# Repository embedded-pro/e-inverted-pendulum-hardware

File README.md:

# e-inverted-pendulum — Hardware

Hardware for the [e-inverted-pendulum](https://github.com/embedded-pro/e-inverted-pendulum) two-wheeled self-balancing
robot. The PCB is the robot's chassis: one vertical 85 × 130 mm 4-layer board carries the electronics, the battery and
the motor bracket. Built and assembled at JLCPCB.

This repository holds the **KiCad** design, the Python scripts that generate the schematic and sync the board, and the
ngspice simulation suite. The firmware lives in its own repository and is the source of the requirements.

> **Status: Phase 3 (layout), placement handed to the owner (D-032).** Phases 0–2 (requirements, schematic,
> simulation) are signed off. The schematic is complete, simulated and ERC-clean; the board has its outline, rule
> areas and bracket holes, with every part in the staging area. See [docs/plan.md](docs/plan.md) for the phase gates.

---

## Highlights

- **STM32WB55RGV6** with BLE 5: internal SMPS, 32 MHz HSE without external caps, printed IFA through an
  `MLPF-WB55-01E3` filter on a 50 Ω GCPW line, DNP pi tuning and a DNP U.FL test port.
- **DRV8711 gate driver with four external half-bridges** (`CSD88537ND`) for two MG310 gear motors: indexer bypassed
  (PWMMODE 1), 50 mΩ low-side shunts with Kelvin taps, 2.0 A trip, SS34 clamps on every phase node.
- **Battery path:** XT30, 4 A fuse, back-to-back `AO4805` P-FETs for reverse polarity and switching, with a simulated
  Miller soft start; `SMBJ15A` after the FETs.
- **Rails:** `TPS62933F` buck to 5 V (encoders, RGB LEDs, LDO), `TLV75533P` LDO to 3.3 V, ferrite-filtered VDDA.
- **12 RGB LEDs** (`WS2812B-2020-V6`) on one PA7 timer/DMA pin through a 5 V `SN74AHCT1G125`: it is also a toy (D-035).
  No buttons, no buzzer.
- **Test pads** on every sheet (rails, motor phases and shunts, PWM, SPI, encoders, IMU, I2C), net names on the silk.
- **Sensors and storage:** `MPU-6500` IMU on SPI2, `W25Q16JV` flash on SPI1, `M24C64` EEPROM and an `ST25DV04KC` NFC tag
  with a printed 13.56 MHz coil on I2C3, plus a Qwiic port.
- **Encoder inputs:** ESD at the connector, 100 Ω + 1 nF, `SN74LVC3G17` Schmitt buffers with 5 V-tolerant inputs.

---

## Board architecture

The schematic has 8 hierarchical sheets, one functional block each, drawn as titled boxes with design notes (the
e-psu-hardware pattern, D-033):

| Sheet | Function | Key parts |
|-------|----------|-----------|
| `e-inverted-pendulum.kicad_sch` | Root: sheet descriptions, power flow, grounding | — |
| `power_entry` | Battery input, fuse, power switch with soft start, TVS, VBAT sense | `AO4805`, `SMBJ15A`, XT30 |
| `logic_power` | 5V0 buck and 3V3 LDO | `TPS62933F`, `TLV75533P` |
| `mcu` | MCU pin map, decoupling, SMPS, clocks, reset/boot, STDC14 debug | `STM32WB55RGV6` |
| `rf` | 2.4 GHz path and printed antenna | `MLPF-WB55-01E3` |
| `drive` | Gate driver, four half-bridges, current sense | `DRV8711`, `CSD88537ND` |
| `motors_encoders` | Motor + encoder connectors, encoder conditioning | JST PH 6-pin, `TPD4E05U06`, `SN74LVC3G17` |
| `imu_flash` | IMU and SPI flash | `MPU-6500`, `W25Q16JV` |
| `ui` | Status LED, 12 RGB LEDs, Qwiic, EEPROM, NFC tag | `WS2812B-2020-V6`, `SN74AHCT1G125`, `M24C64`, `ST25DV04KC` |

---

## Design requirements

The firmware is the requirement source. [docs/requirements.md](docs/requirements.md) traces every hardware
requirement to a firmware `REQ-*` ID or to a decision in [docs/decisions.md](docs/decisions.md). The key targets:

| Item | Target | Source |
|------|--------|--------|
| Battery | 3S LiPo, 9.0–12.6 V, XT30, reverse-polarity protected | D-011, D-021 |
| Motors | 2 × MG310 1:20 (7.4 V), average motor voltage capped at 7.4 V by firmware | D-027 |
| Drive | DRV8711, PWMMODE 1, trip 2.0 A (ISGAIN 20, TORQUE 186), 0.5 A continuous by firmware I²t | D-027, S0 |
| Encoders | Hall A/B, no index; 1040 counts per wheel revolution (13 PPR is an assumption) | D-028 |
| Radio | BLE on the STM32WB55, printed IFA | D-001, D-007 |
| PCB | 85 × 130 mm, 4 layers JLC04161H-7628, L2 solid GND, JLCPCB assembly | D-008, D-024 |

[docs/firmware-interface.md](docs/firmware-interface.md) lists the settings the firmware must apply (DRV8711 registers,
voltage cap, ADC scaling, clock trims, I2C addresses).

### Simulation

`python3 simulation/run_all.py` runs S0–S5 (motor sizing, power entry, H-bridge switching, bus ripple, rails, ADC and
encoder edges). Two power-entry failures and one phase-node abs-max violation were found and fixed in the schematic.
Details: [simulation/REPORT.md](simulation/REPORT.md).

---

## Repository layout

```
e-inverted-pendulum-hardware/
├── hardware/
│   └── e-inverted-pendulum/          # KiCad 10 project
│       ├── e-inverted-pendulum.kicad_pro / .kicad_sch (root) / .kicad_pcb / .kicad_dru
│       ├── power_entry / logic_power / mcu / rf / drive / motors_encoders / imu_flash / ui .kicad_sch
│       ├── e-inverted-pendulum.kicad_sym    # project symbols
│       ├── e-inverted-pendulum.pretty/      # project footprints (XT30, STDC14, NFC coil, ...)
│       └── sym-lib-table, fp-lib-table
├── scripts/
│   ├── schgen/                       # schematic generator: design/*.py -> hardware/ (D-020, D-033)
│   ├── pcb/                          # board sync from the schematic (add-only, D-032) and renders
│   ├── export_review.py              # review package     -> review_exports/<board>/
│   ├── export_jlcpcb.py              # fab + assembly     -> manufacturing/<board>/
│   ├── export_release.py             # release bundle     -> release/<board>-<version>.zip
│   ├── visual_diff.py                # PR visual diff     -> diff/<board>/
│   └── check_*.py, design_calcs.py, nfc_coil.py, gcpw.py, export_bom.py, jlc_stock.py
├── simulation/                       # ngspice suite (S0–S5) + REPORT.md
├── pin-data/                         # pin map and the DS11929 package data it is checked against
├── bom/                              # part catalogue, BOM, stock check
├── docs/
│   ├── plan.md, requirements.md, decisions.md, design-calcs.md, power-map.md, rf.md, nfc.md, layout.md, ...
│   ├── robot-hardware-design-guide.md    # design and review knowledge base
│   ├── schematic.pdf
│   └── images/                       # board renders
├── .claude/agents/pendulum-board-reviewer.md   # design-review agent
├── PROJECT_CONTEXT.md                # design summary, decisions, open items
└── .github/workflows/                # hardware checks, kicad-bot, visual diff, release
```

Generated outputs are gitignored: `review_exports/`, `manufacturing/`, `release/`, `diff/`.

---

## Getting started

KiCad 10 project. Open `hardware/e-inverted-pendulum/e-inverted-pendulum.kicad_pro`.

```bash
git clone https://github.com/embedded-pro/e-inverted-pendulum-hardware.git
```

### Headless checks (the same ones CI runs)

```bash
python3 scripts/check_pinmap.py --firmware ../e-inverted-pendulum
```

```bash
python3 scripts/schgen/build.py
```

```bash
python3 scripts/schgen/check.py
```

```bash
kicad-cli sch erc --severity-all --exit-code-violations hardware/e-inverted-pendulum/e-inverted-pendulum.kicad_sch
```

```bash
python3 scripts/check_netlist.py && python3 scripts/check_library.py
```

### Changing the schematic

The schematic is generated: edit `scripts/schgen/design/<sheet>.py`, then rebuild. `scripts/schgen/render.sh` rebuilds,
checks the netlist against `expected.json`, writes `docs/schematic.pdf` and renders each sheet to PNG. After a
drawing-only change, prove the circuit is unchanged against the last commit:

```bash
python3 scripts/schgen/check_equivalence.py HEAD
```

Then bring the board in line (new parts land in the staging area; nothing on the board moves):

```bash
python3 scripts/pcb/board.py --rules <path to pcb_rules.py from the pcb-design-rules skill>
```

### Review and fabrication packages

- `python3 scripts/export_review.py`: ERC/DRC, netlist, BOM, PDFs and renders for a design review, used by the
  `pendulum-board-reviewer` agent in [`.claude/agents/`](.claude/agents/).
- `python3 scripts/export_jlcpcb.py`: Gerbers, drill, BOM and CPL for JLCPCB.
- `python3 scripts/export_bom.py` then `python3 scripts/jlc_stock.py bom/bom.csv --boards 5`: BOM and live stock.

---

## Before ordering

1. Finish Phase 3: placement (owner), routing, DRC clean with schematic parity, the `power-pcb-layout` §7 and
   `rf-layout` §12 checklists ([docs/plan.md](docs/plan.md)).
2. Re-run the stock check; every line must be in stock for the order quantity.
3. JLCPCB options (PCB + assembly, D-036): 4 layers, JLC04161H-7628, 1.6 mm, 1 oz outer / 0.5 oz inner; impedance
   control, 50 Ω ±10 % on the L1 GCPW over L2 (0.27 / 0.15 mm, `docs/rf.md`). Check every CPL rotation in the preview
   (the WS2812B-2020 footprint is the datasheet pattern turned 180°).
4. Leave the DNP parts off: pi tuning C401/C402, U.FL J401 + R402, NFC trim C804, sense filters C501/C504, motor
   snubbers C603/C607, encoder pull-ups, R602.

---

## Continuous integration

- [`hardware.yml`](.github/workflows/hardware.yml): pin map, regenerate the schematic with no diff, netlist against
  the generator's intent, ERC, netlist and symbol/footprint checks.
- [`kicad-bot.yml`](.github/workflows/kicad-bot.yml): [kicad-bot](https://github.com/embedded-pro/kicad-bot) ERC/DRC
  with schematic parity, on pushes to `main` and on pull requests; DRC does not fail the build until the board is
  routed. kicad-bot runs without KiCad's libraries, so its ERC shows library-lookup warnings; `hardware.yml` is the
  library check.
- [`kicad-diff.yml`](.github/workflows/kicad-diff.yml): red/green visual diff of schematic and board on pull requests.
- KiCad on GitHub runners: `scripts/install_kicad.sh 10` (and kicad-bot ≥ v0.1.5) pins the KiCad PPA to `amd64`.
  Ubuntu 26.04 runners otherwise install Ubuntu's KiCad 9, which can't open this project; the script fails if
  `kicad-cli` isn't 10.x.
- [`release.yml`](.github/workflows/release.yml): [release-please](https://github.com/googleapis/release-please) from
  Conventional Commits; each release attaches the fabrication bundle from `scripts/export_release.py`.

Third-party actions are pinned to a full commit SHA. CI is a guardrail, not a design review: use the
`pendulum-board-reviewer` agent with [docs/robot-hardware-design-guide.md](docs/robot-hardware-design-guide.md) for that.

Design rules come from the `hardware-design` skills in
[claude-hardware-skills](https://github.com/gabrielfrasantos/claude-hardware-skills).

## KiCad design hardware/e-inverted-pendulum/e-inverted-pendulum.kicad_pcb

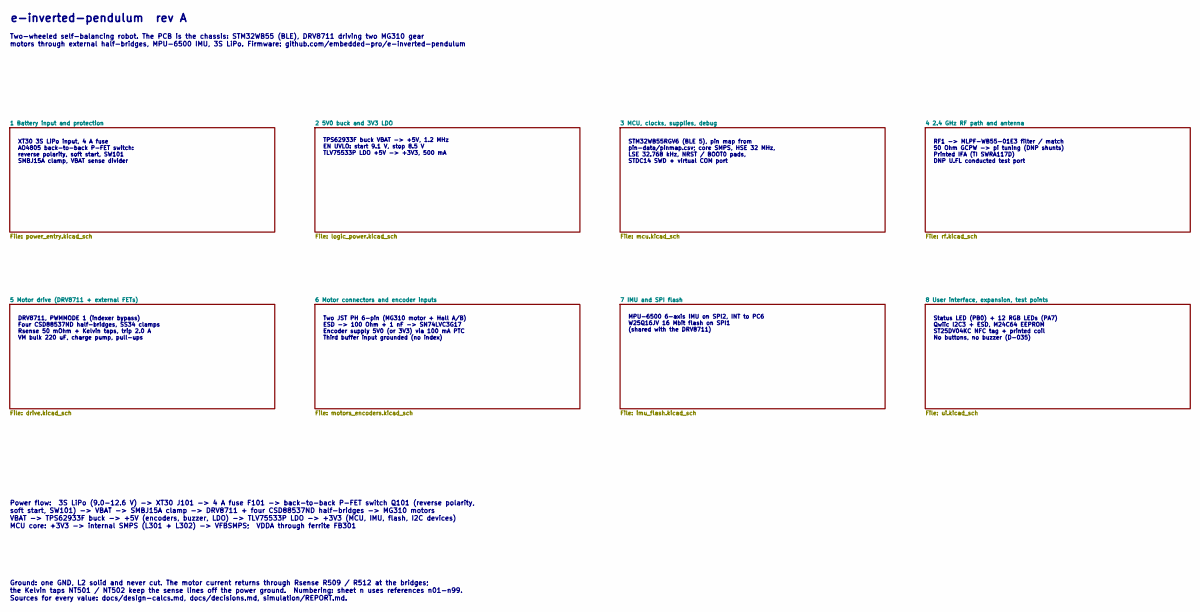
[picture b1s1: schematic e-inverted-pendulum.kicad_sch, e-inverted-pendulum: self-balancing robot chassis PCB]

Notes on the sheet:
Two JST PH 6-pin (MG310 motor + Hall A/B) ESD -> 100 Ohm + 1 nF -> SN74LVC3G17 Encoder supply 5V0 (or 3V3) via 100 mA PTC Third buffer input grounded (no index)
DRV8711, PWMMODE 1 (indexer bypass) Four CSD88537ND half-bridges, SS34 clamps Rsense 50 mOhm + Kelvin taps, trip 2.0 A VM bulk 220 uF, charge pump, pull-ups
RF1 -> MLPF-WB55-01E3 filter / match 50 Ohm GCPW -> pi tuning (DNP shunts) Printed IFA (TI SWRA117D) DNP U.FL conducted test port
MPU-6500 6-axis IMU on SPI2, INT to PC6 W25Q16JV 16 Mbit flash on SPI1 (shared with the DRV8711)
Status LED (PB0) + 12 RGB LEDs (PA7) Qwiic I2C3 + ESD, M24C64 EEPROM ST25DV04KC NFC tag + printed coil No buttons, no buzzer (D-035)
Two-wheeled self-balancing robot. The PCB is the chassis: STM32WB55 (BLE), DRV8711 driving two MG310 gear motors through external half-bridges, MPU-6500 IMU, 3S LiPo. Firmware: github.com/embedded-pro/e-inverted-pendulum
XT30 3S LiPo input, 4 A fuse AO4805 back-to-back P-FET switch: reverse polarity, soft start, SW101 SMBJ15A clamp, VBAT sense divider
e-inverted-pendulum rev A
TPS62933F buck VBAT -> +5V, 1.2 MHz EN UVLO: start 9.1 V, stop 8.5 V TLV75533P LDO +5V -> +3V3, 500 mA
Ground: one GND, L2 solid and never cut. The motor current returns through Rsense R509 / R512 at the bridges; the Kelvin taps NT501 / NT502 keep the sense lines off the power ground. Numbering: sheet n uses references n01-n99. Sources for every value: docs/design-calcs.md, docs/decisions.md, simula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
STM32WB55RGV6 (BLE 5), pin map from pin-data/pinmap.csv; core SMPS, HSE 32 MHz, LSE 32.768 kHz, NRST / BOOT0 pads, STDC14 SWD + virtual COM port
Power flow: 3S LiPo (9.0-12.6 V) -> XT30 J101 -> 4 A fuse F101 -> back-to-back P-FET switch Q101 (reverse polarity, soft start, SW101) -> VBAT -> SMBJ15A clamp -> DRV8711 + four CSD88537ND half-bridges -> MG310 motors VBAT -> TPS62933F buck -> +5V (encoders, buzzer, LDO) -> TLV75533P LDO -> +3V3 (M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

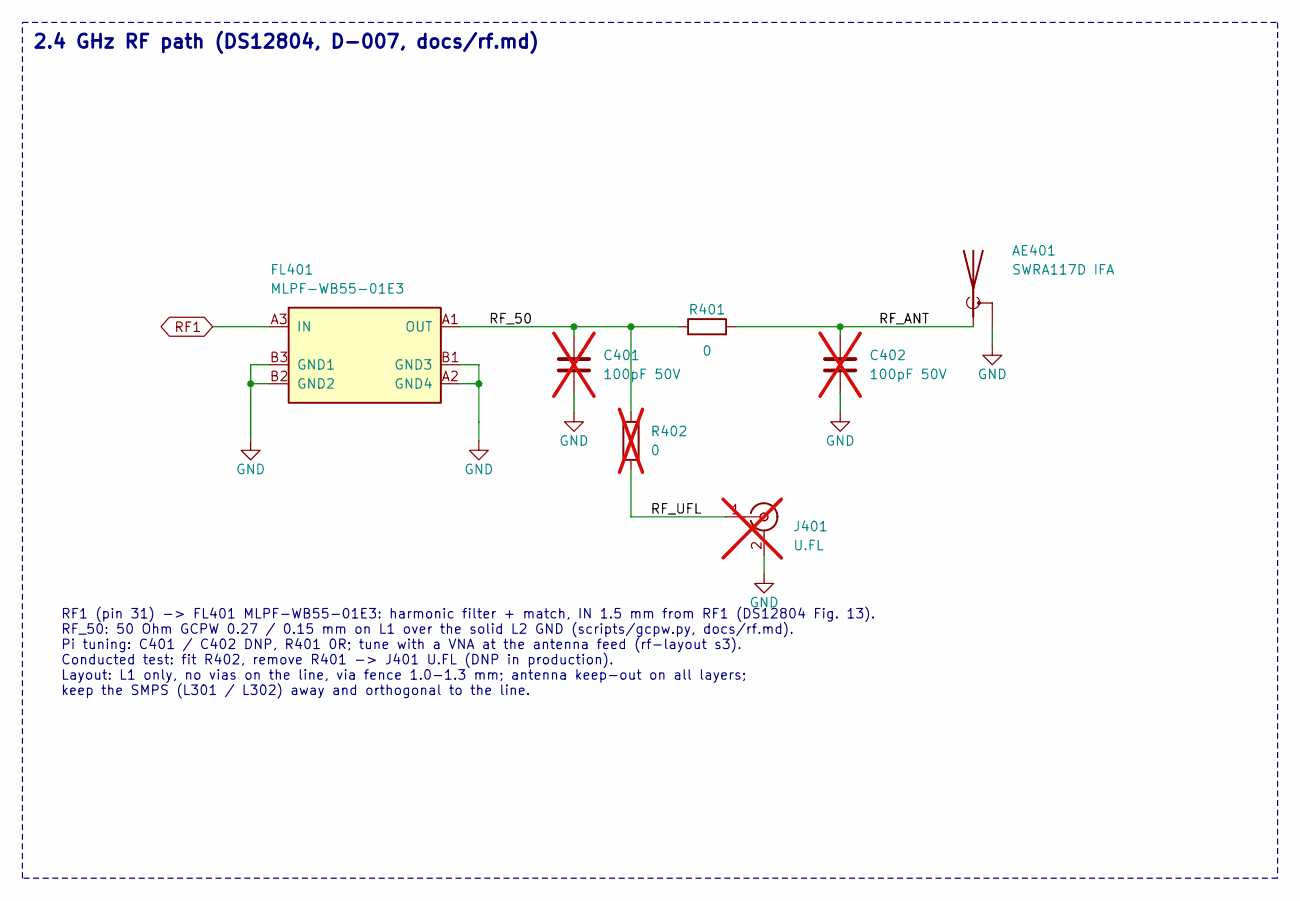
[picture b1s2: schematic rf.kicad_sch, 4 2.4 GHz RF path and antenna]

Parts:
AE401: SWRA117D IFA; Texas_SWRA117D_2.4GHz_Left
C401, C402: 100pF 50V; C_0402_1005Metric; MPN CL05C101JB5NNNC; LCSC C26409; not fitted
FL401: MLPF-WB55-01E3; ST_MLPF-WB55-01E3; MPN MLPF-WB55-01E3; LCSC C2651048
J401: U.FL; U.FL_Hirose_U.FL-R-SMT-1_Vertical; MPN BWU.FL-IPEX1; LCSC C5137195; not fitted
R401: 0; R_0402_1005Metric; MPN 0402WGF0000TCE; LCSC C17168
R402: 0; R_0402_1005Metric; MPN 0402WGF0000TCE; LCSC C17168; not fitted

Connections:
/4 2.4 GHz RF path and antenna/RF_50: C401.1, FL401.A1 (OUT), R401.1, R402.1
/4 2.4 GHz RF path and antenna/RF_ANT: AE401.1 (A), C402.1, R401.2
/4 2.4 GHz RF path and antenna/RF_UFL: J401.1 (In), R402.2
GND: AE401.2 (Shield), C401.2, C402.2, FL401.A2 (GND4), FL401.B1 (GND3), FL401.B2 (GND2), FL401.B3 (GND1), J401.2 (Ext); also elsewhere on the board
RF1: FL401.A3 (IN); also elsewhere on the board

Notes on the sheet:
2.4 GHz RF path (DS12804, D-007, docs/rf.md)
RF1 (pin 31) -> FL401 MLPF-WB55-01E3: harmonic filter + match, IN 1.5 mm from RF1 (DS12804 Fig. 13). RF_50: 50 Ohm GCPW 0.27 / 0.15 mm on L1 over the solid L2 GND (scripts/gcpw.py, docs/rf.md). Pi tuning: C401 / C402 DNP, R401 0R; tune with a VNA at the antenna feed (rf-layout s3). Conducted test: 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

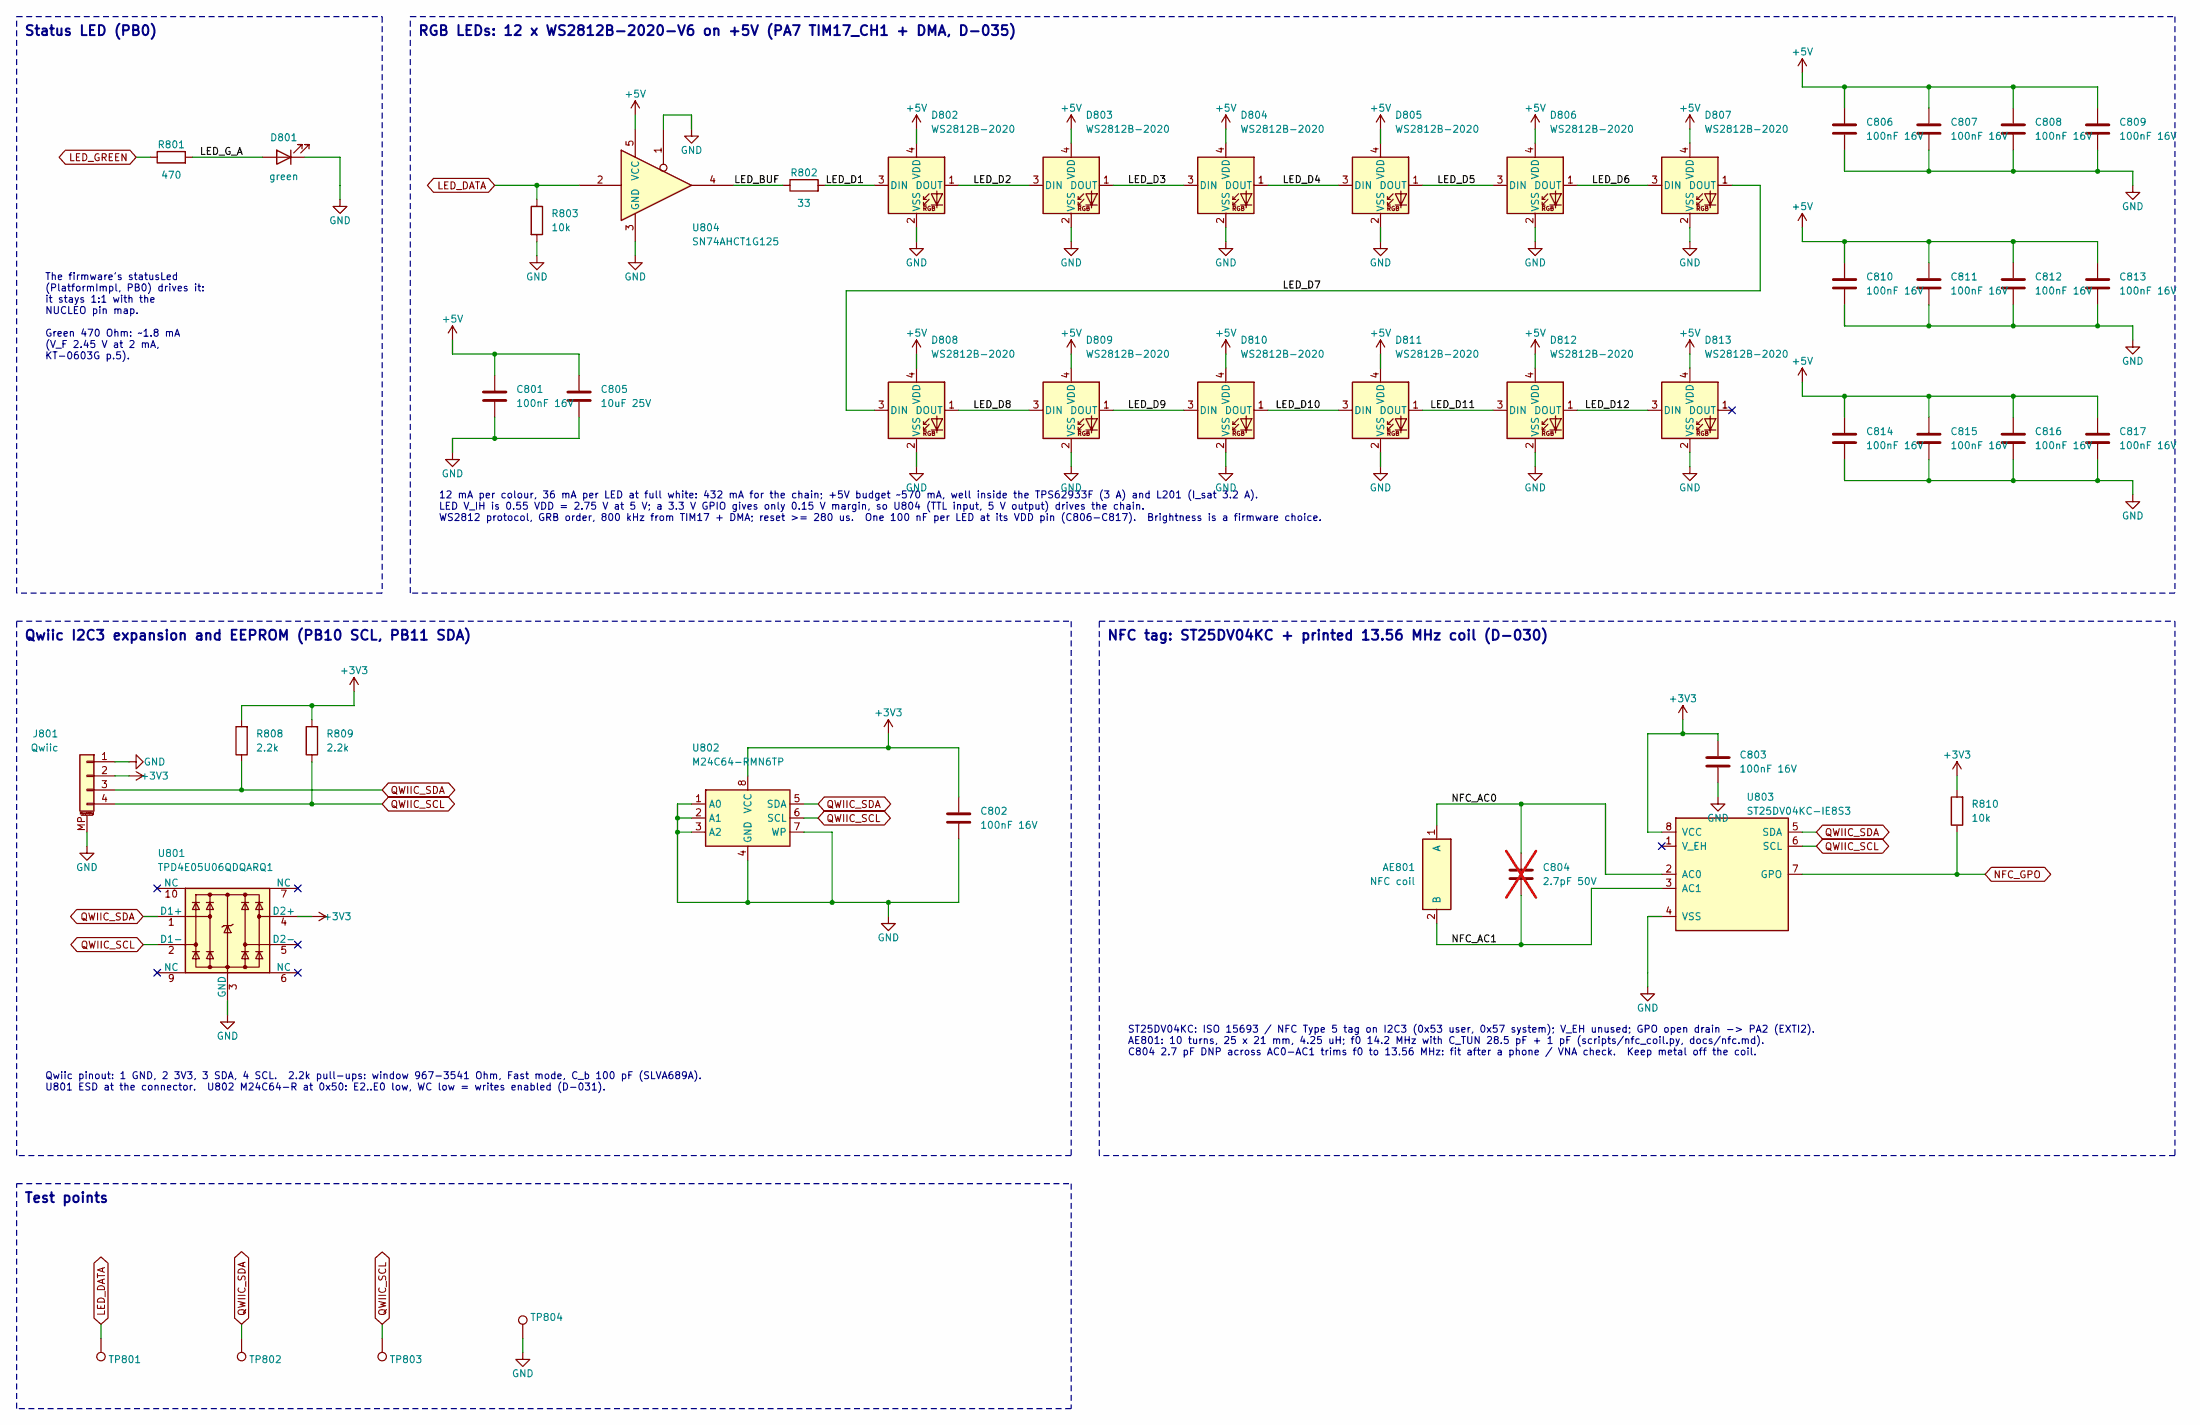
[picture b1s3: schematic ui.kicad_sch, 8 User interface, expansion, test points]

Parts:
AE801: NFC coil; NFC_Coil_25x21mm
C801, C802, C803, C806, C807, C808, C809, C810, C811, C812, C813, C814, C815, C816, C817: 100nF 16V; C_0402_1005Metric; MPN CL05B104KO5NNNC; LCSC C1525
C804: 2.7pF 50V; C_0402_1005Metric; MPN CL05C2R7CB5NNNC; LCSC C318593; not fitted
C805: 10uF 25V; C_0805_2012Metric; MPN CL21A106KAYNNNE; LCSC C15850
D801: green; LED_0603_1608Metric; MPN KT-0603G; LCSC C12624
D802, D803, D804, D805, D806, D807, D808, D809, D810, D811, D812, D813: WS2812B-2020; LED_WS2812B-2020_PLCC4_2.0x2.0mm; MPN WS2812B-2020-V6; LCSC C52917434
J801: Qwiic; JST_SH_SM04B-SRSS-TB_1x04-1MP_P1.00mm_Horizontal; MPN SM04B-SRSS-TB(LF)(SN); LCSC C160404
R801: 470; R_0603_1608Metric; MPN 0603WAF4700T5E; LCSC C23179
R802: 33; R_0603_1608Metric; MPN 0603WAF330JT5E; LCSC C23140
R803, R810: 10k; R_0603_1608Metric; MPN 0603WAF1002T5E; LCSC C25804
R808, R809: 2.2k; R_0603_1608Metric; MPN 0603WAF2201T5E; LCSC C4190
TP801: LED_DATA; TestPoint_Pad_D1.0mm
TP802: QWIIC_SDA; TestPoint_Pad_D1.0mm
TP803: QWIIC_SCL; TestPoint_Pad_D1.0mm
TP804: GND; TestPoint_Pad_D1.5mm
U801: TPD4E05U06QDQARQ1; USON-10_2.5x1.0mm_P0.5mm; MPN TPD4E05U06QDQARQ1; LCSC C81353
U802: M24C64-RMN6TP; SOIC-8_3.9x4.9mm_P1.27mm; MPN M24C64-RMN6TP; LCSC C79988
U803: ST25DV04KC-IE8S3; SOIC-8_3.9x4.9mm_P1.27mm; MPN ST25DV04KC-IE8S3; LCSC C5221752
U804: SN74AHCT1G125; SOT-23-5; MPN SN74AHCT1G125DBVR; LCSC C7484

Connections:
+3V3: C802.1, C803.1, J801.2, R808.2, R809.2, R810.2, U801.4 (D2+), U802.8 (VCC), U803.8 (VCC); also elsewhere on the board
+5V: C801.1, C805.1, C806.1, C807.1, C808.1, C809.1, C810.1, C811.1, C812.1, C813.1, C814.1, C815.1, C816.1, C817.1, D802.4 (VDD), D803.4 (VDD), D804.4 (VDD), D805.4 (VDD), D806.4 (VDD), D807.4 (VDD), D808.4 (VDD), D809.4 (VDD), D810.4 (VDD), D811.4 (VDD), D812.4 (VDD), D813.4 (VDD), U804.5 (VCC); also elsewhere on the board
/8 User interface, expansion, test points/LED_BUF: R802.1, U804.4
/8 User interface, expansion, test points/LED_D1: D802.3 (DIN), R802.2
/8 User interface, expansion, test points/LED_D2: D802.1 (DOUT), D803.3 (DIN)
/8 User interface, expansion, test points/LED_D3: D803.1 (DOUT), D804.3 (DIN)
/8 User interface, expansion, test points/LED_D4: D804.1 (DOUT), D805.3 (DIN)
/8 User interface, expansion, test points/LED_D5: D805.1 (DOUT), D806.3 (DIN)
/8 User interface, expansion, test points/LED_D6: D806.1 (DOUT), D807.3 (DIN)
/8 User interface, expansion, test points/LED_D7: D807.1 (DOUT), D808.3 (DIN)
/8 User interface, expansion, test points/LED_D8: D808.1 (DOUT), D809.3 (DIN)
/8 User interface, expansion, test points/LED_D9: D809.1 (DOUT), D810.3 (DIN)
/8 User interface, expansion, test points/LED_D10: D810.1 (DOUT), D811.3 (DIN)
/8 User interface, expansion, test points/LED_D11: D811.1 (DOUT), D812.3 (DIN)
/8 User interface, expansion, test points/LED_D12: D812.1 (DOUT), D813.3 (DIN)
/8 User interface, expansion, test points/LED_G_A: D801.2 (A), R801.2
/8 User interface, expansion, test points/NFC_AC0: AE801.1 (A), C804.1, U803.2 (AC0)
/8 User interface, expansion, test points/NFC_AC1: AE801.2 (B), C804.2, U803.3 (AC1)
GND: C801.2, C802.2, C803.2, C805.2, C806.2, C807.2, C808.2, C809.2, C810.2, C811.2, C812.2, C813.2, C814.2, C815.2, C816.2, C817.2, D801.1 (K), D802.2 (VSS), D803.2 (VSS), D804.2 (VSS), D805.2 (VSS), D806.2 (VSS), D807.2 (VSS), D808.2 (VSS), D809.2 (VSS), D810.2 (VSS), D811.2 (VSS), D812.2 (VSS), D813.2 (VSS), J801.1, J801.MP (MountPin), R803.2, TP804.1, U801.3 (GND), U801.8 (GND), U802.1 (A0), U802.2 (A1), U802.3 (A2), U802.4 (GND), U802.7 (WP), U803.4 (VSS), U804.1, U804.3 (GND); also elsewhere on the board
LED_DATA: R803.1, TP801.1, U804.2; also elsewhere on the board
LED_GREEN: R801.1; also elsewhere on the board
NFC_GPO: R810.1, U803.7 (GPO); also elsewhere on the board
QWIIC_SCL: J801.4, R809.1, TP803.1, U801.2 (D1-), U802.6 (SCL), U803.6 (SCL); also elsewhere on the board
QWIIC_SDA: J801.3, R808.1, TP802.1, U801.1 (D1+), U802.5 (SDA), U803.5 (SDA); also elsewhere on the board

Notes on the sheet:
NFC tag: ST25DV04KC + printed 13.56 MHz coil (D-030)
Status LED (PB0)
RGB LEDs: 12 x WS2812B-2020-V6 on +5V (PA7 TIM17_CH1 + DMA, D-035)
Test points
Qwiic pinout: 1 GND, 2 3V3, 3 SDA, 4 SCL. 2.2k pull-ups: window 967-3541 Ohm, Fast mode, C_b 100 pF (SLVA689A). U801 ESD at the connector. U802 M24C64-R at 0x50: E2..E0 low, WC low = writes enabled (D-031).
The firmware's statusLed (PlatformImpl, PB0) drives it: it stays 1:1 with the NUCLEO pin map. Green 470 Ohm: ~1.8 mA (V_F 2.45 V at 2 mA, KT-0603G p.5).
12 mA per colour, 36 mA per LED at full white: 432 mA for the chain; +5V budget ~570 mA, well inside the TPS62933F (3 A) and L201 (I_sat 3.2 A). LED V_IH is 0.55 VDD = 2.75 V at 5 V; a 3.3 V GPIO gives only 0.15 V margin, so U804 (TTL input, 5 V output) drives the chain. WS2812 protocol, GRB order,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
ST25DV04KC: ISO 15693 / NFC Type 5 tag on I2C3 (0x53 user, 0x57 system); V_EH unused; GPO open drain -> PA2 (EXTI2). AE801: 10 turns, 25 x 21 mm, 4.25 uH; f0 14.2 MHz with C_TUN 28.5 pF + 1 pF (scripts/nfc_coil.py, docs/nfc.md). C804 2.7 pF DNP across AC0-AC1 trims f0 to 13.56 MHz: fit after a phon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
Qwiic I2C3 expansion and EEPROM (PB10 SCL, PB11 SDA)

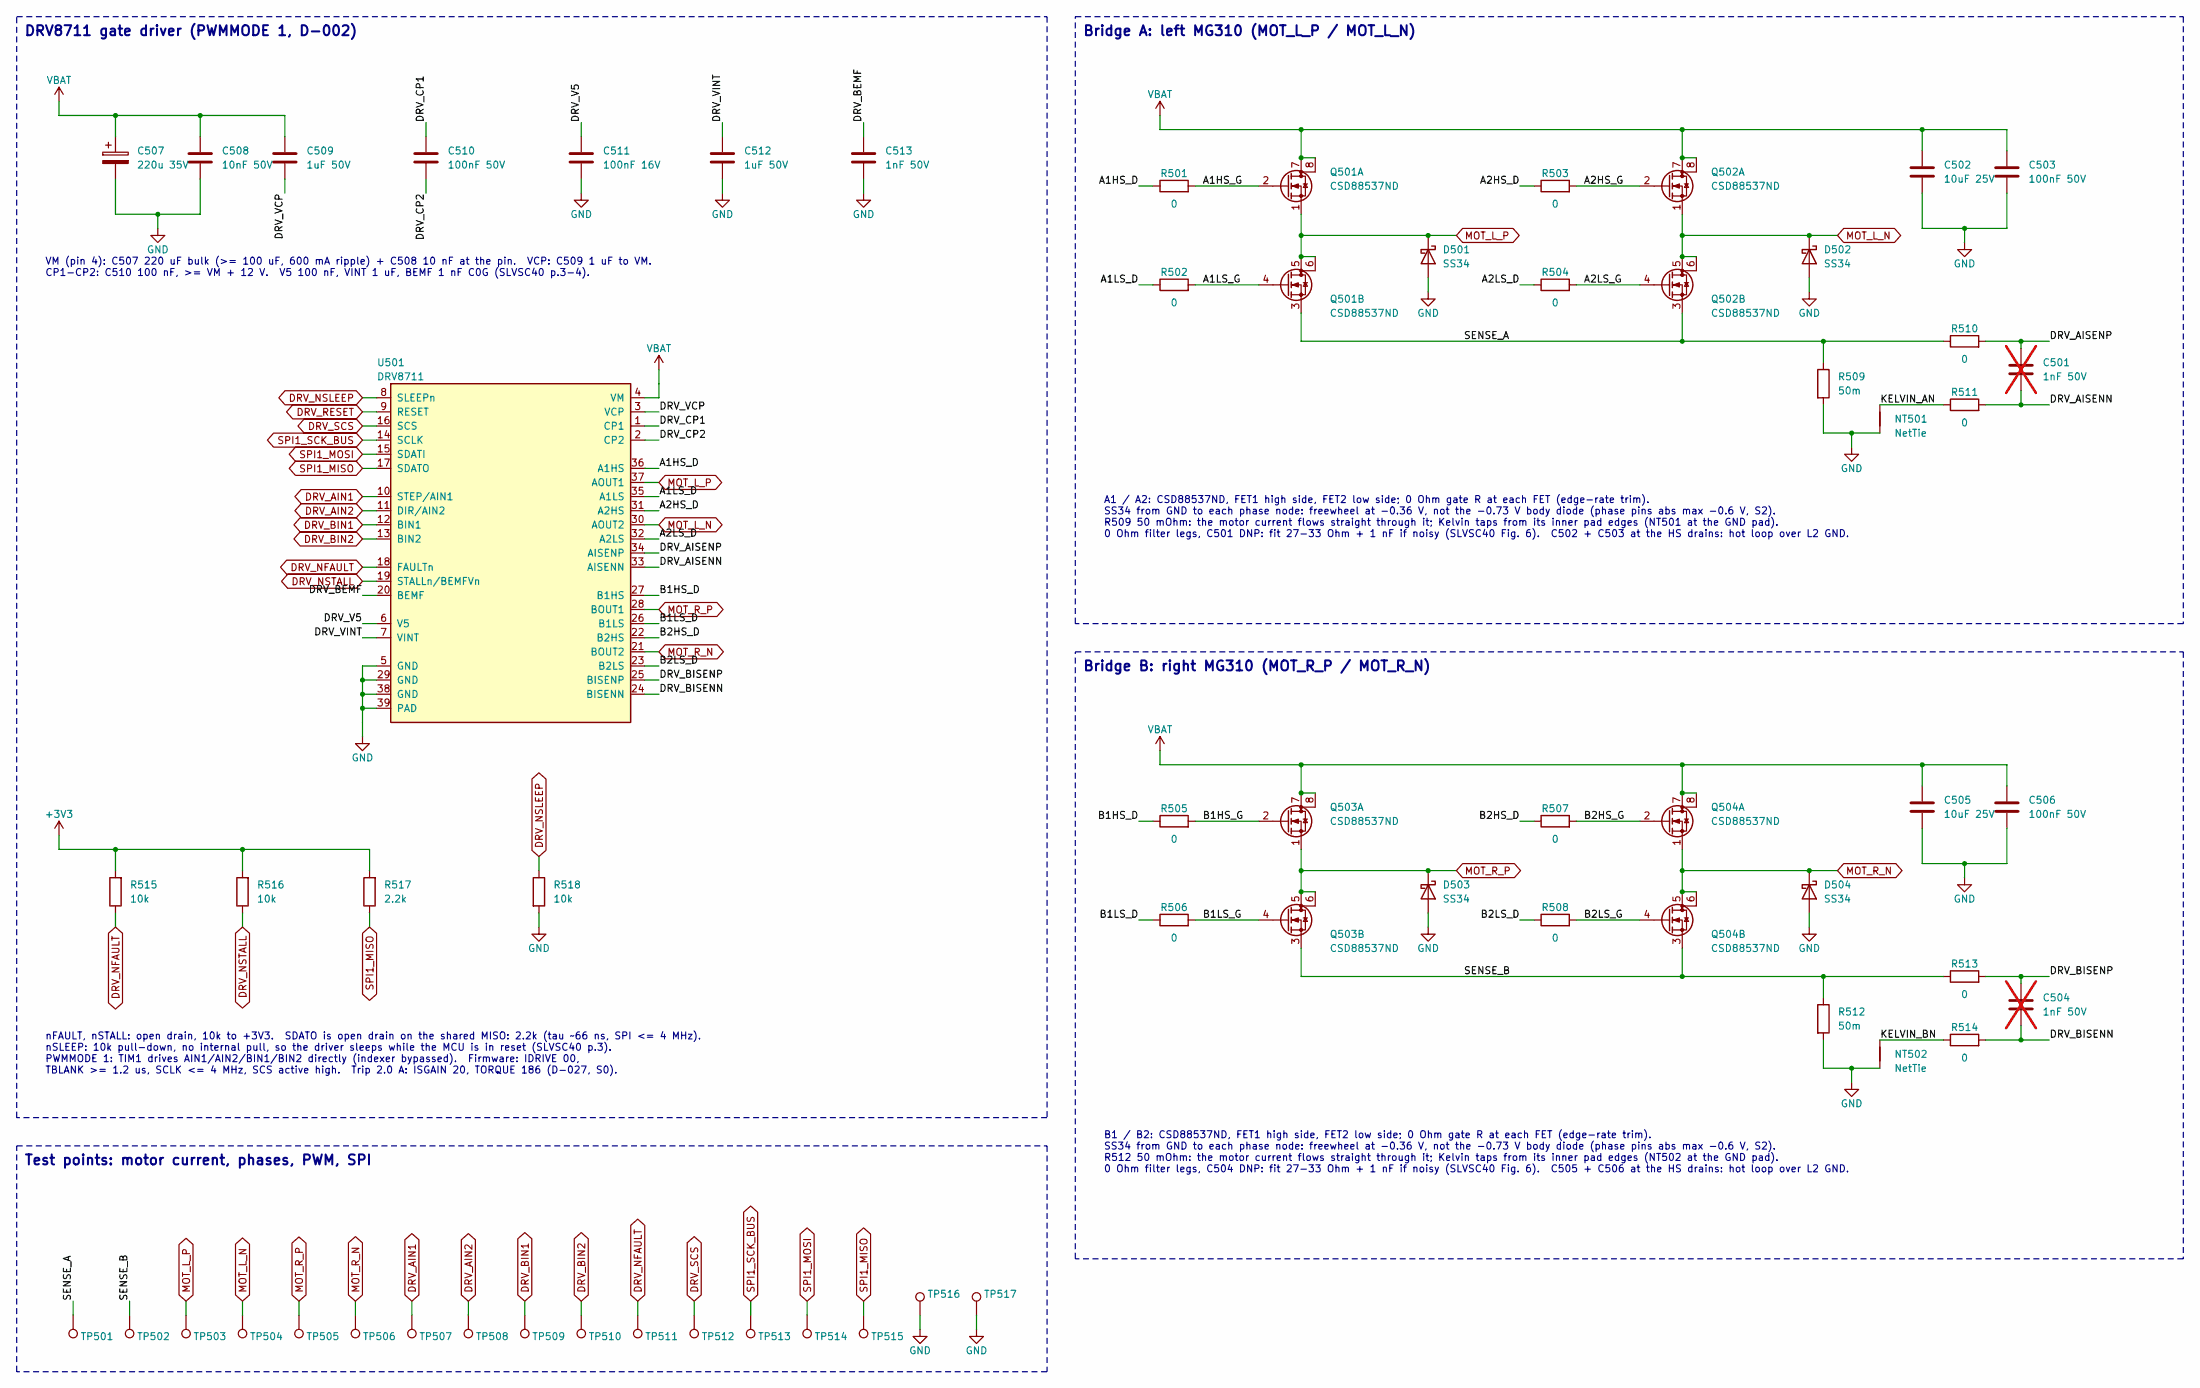
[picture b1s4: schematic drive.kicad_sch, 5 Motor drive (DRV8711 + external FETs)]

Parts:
C501, C504: 1nF 50V; C_0402_1005Metric; MPN CL05C102JB5NNNC; LCSC C307441; not fitted
C502, C505: 10uF 25V; C_0805_2012Metric; MPN CL21A106KAYNNNE; LCSC C15850
C503, C506, C510: 100nF 50V; C_0603_1608Metric; MPN CC0603KRX7R9BB104; LCSC C14663
C507: 220u 35V; CP_Elec_8x10; MPN EEEFK1V221P; LCSC C178562
C508: 10nF 50V; C_0603_1608Metric; MPN CL10B103KB8NNNC; LCSC C1589
C509, C512: 1uF 50V; C_0603_1608Metric; MPN CL10A105KB8NNNC; LCSC C15849
C511: 100nF 16V; C_0402_1005Metric; MPN CL05B104KO5NNNC; LCSC C1525
C513: 1nF 50V; C_0402_1005Metric; MPN CL05C102JB5NNNC; LCSC C307441
D501, D502, D503, D504: SS34; D_SMA; MPN SS34; LCSC C8678
NT501, NT502: NetTie; NetTie-2_SMD_Pad0.5mm
Q501, Q502, Q503, Q504: CSD88537ND; SOIC-8_3.9x4.9mm_P1.27mm; MPN CSD88537ND; LCSC C117439
R501, R502, R503, R504, R505, R506, R507, R508, R510, R511, R513, R514: 0; R_0603_1608Metric; MPN 0603WAF0000T5E; LCSC C21189
R509, R512: 50m; R_1206_3216Metric; MPN HoLR1206-1W-50mR-1%-75ppm; LCSC C601102
R515, R516, R518: 10k; R_0603_1608Metric; MPN 0603WAF1002T5E; LCSC C25804
R517: 2.2k; R_0603_1608Metric; MPN 0603WAF2201T5E; LCSC C4190
TP501: SENSE_A; TestPoint_Pad_D1.0mm
TP502: SENSE_B; TestPoint_Pad_D1.0mm
TP503: MOT_L_P; TestPoint_Pad_D1.0mm
TP504: MOT_L_N; TestPoint_Pad_D1.0mm
TP505: MOT_R_P; TestPoint_Pad_D1.0mm
TP506: MOT_R_N; TestPoint_Pad_D1.0mm
TP507: DRV_AIN1; TestPoint_Pad_D1.0mm
TP508: DRV_AIN2; TestPoint_Pad_D1.0mm
TP509: DRV_BIN1; TestPoint_Pad_D1.0mm
TP510: DRV_BIN2; TestPoint_Pad_D1.0mm
TP511: DRV_NFAULT; TestPoint_Pad_D1.0mm
TP512: DRV_SCS; TestPoint_Pad_D1.0mm
TP513: SPI1_SCK_BUS; TestPoint_Pad_D1.0mm
TP514: SPI1_MOSI; TestPoint_Pad_D1.0mm
TP515: SPI1_MISO; TestPoint_Pad_D1.0mm
TP516, TP517: GND; TestPoint_Pad_D1.5mm
U501: DRV8711; HTSSOP-38-1EP_4.4x9.7mm_P0.5mm_EP2.74x4.75mm_ThermalVias; MPN DRV8711DCPR; LCSC C60013

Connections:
+3V3: R515.2, R516.2, R517.2; also elsewhere on the board
/5 Motor drive (DRV8711 + external FETs)/A1HS_D: R501.1, U501.36 (A1HS)
/5 Motor drive (DRV8711 + external FETs)/A1HS_G: Q501.2 (G), R501.2
/5 Motor drive (DRV8711 + external FETs)/A1LS_D: R502.1, U501.35 (A1LS)
/5 Motor drive (DRV8711 + external FETs)/A1LS_G: Q501.4 (G), R502.2
/5 Motor drive (DRV8711 + external FETs)/A2HS_D: R503.1, U501.31 (A2HS)
/5 Motor drive (DRV8711 + external FETs)/A2HS_G: Q502.2 (G), R503.2
/5 Motor drive (DRV8711 + external FETs)/A2LS_D: R504.1, U501.32 (A2LS)
/5 Motor drive (DRV8711 + external FETs)/A2LS_G: Q502.4 (G), R504.2
/5 Motor drive (DRV8711 + external FETs)/B1HS_D: R505.1, U501.27 (B1HS)
/5 Motor drive (DRV8711 + external FETs)/B1HS_G: Q503.2 (G), R505.2
/5 Motor drive (DRV8711 + external FETs)/B1LS_D: R506.1, U501.26 (B1LS)
/5 Motor drive (DRV8711 + external FETs)/B1LS_G: Q503.4 (G), R506.2
/5 Motor drive (DRV8711 + external FETs)/B2HS_D: R507.1, U501.22 (B2HS)
/5 Motor drive (DRV8711 + external FETs)/B2HS_G: Q504.2 (G), R507.2
/5 Motor drive (DRV8711 + external FETs)/B2LS_D: R508.1, U501.23 (B2LS)
/5 Motor drive (DRV8711 + external FETs)/B2LS_G: Q504.4 (G), R508.2
/5 Motor drive (DRV8711 + external FETs)/DRV_AISENN: C501.2, R511.2, U501.33 (AISENN)
/5 Motor drive (DRV8711 + external FETs)/DRV_AISENP: C501.1, R510.2, U501.34 (AISENP)
/5 Motor drive (DRV8711 + external FETs)/DRV_BEMF: C513.1, U501.20 (BEMF)
/5 Motor drive (DRV8711 + external FETs)/DRV_BISENN: C504.2, R514.2, U501.24 (BISENN)
/5 Motor drive (DRV8711 + external FETs)/DRV_BISENP: C504.1, R513.2, U501.25 (BISENP)
/5 Motor drive (DRV8711 + external FETs)/DRV_CP1: C510.1, U501.1 (CP1)
/5 Motor drive (DRV8711 + external FETs)/DRV_CP2: C510.2, U501.2 (CP2)
/5 Motor drive (DRV8711 + external FETs)/DRV_V5: C511.1, U501.6 (V5)
/5 Motor drive (DRV8711 + external FETs)/DRV_VCP: C509.1, U501.3 (VCP)
/5 Motor drive (DRV8711 + external FETs)/DRV_VINT: C512.1, U501.7 (VINT)
/5 Motor drive (DRV8711 + external FETs)/KELVIN_AN: NT501.1, R511.1
/5 Motor drive (DRV8711 + external FETs)/KELVIN_BN: NT502.1, R514.1
/5 Motor drive (DRV8711 + external FETs)/SENSE_A: Q501.3 (S), Q502.3 (S), R509.1, R510.1, TP501.1
/5 Motor drive (DRV8711 + external FETs)/SENSE_B: Q503.3 (S), Q504.3 (S), R512.1, R513.1, TP502.1
DRV_AIN1: TP507.1, U501.10 (STEP/AIN1); also elsewhere on the board
DRV_AIN2: TP508.1, U501.11 (DIR/AIN2); also elsewhere on the board
DRV_BIN1: TP509.1, U501.12 (BIN1); also elsewhere on the board
DRV_BIN2: TP510.1, U501.13 (BIN2); also elsewhere on the board
DRV_NFAULT: R515.1, TP511.1, U501.18 (FAULTn); also elsewhere on the board
DRV_NSLEEP: R518.1, U501.8 (SLEEPn); also elsewhere on the board
DRV_NSTALL: R516.1, U501.19 (STALLn/BEMFVn); also elsewhere on the board
DRV_RESET: U501.9 (RESET); also elsewhere on the board
DRV_SCS: TP512.1, U501.16 (SCS); also elsewhere on the board
GND: C502.2, C503.2, C505.2, C506.2, C507.2, C508.2, C511.2, C512.2, C513.2, D501.2 (A), D502.2 (A), D503.2 (A), D504.2 (A), NT501.2, NT502.2, R509.2, R512.2, R518.2, TP516.1, TP517.1, U501.5 (GND), U501.29 (GND), U501.38 (GND), U501.39 (PAD); also elsewhere on the board
MOT_L_N: D502.1 (K), Q502.1 (S), Q502.5 (D), Q502.6 (D), TP504.1, U501.30 (AOUT2); also elsewhere on the board
MOT_L_P: D501.1 (K), Q501.1 (S), Q501.5 (D), Q501.6 (D), TP503.1, U501.37 (AOUT1); also elsewhere on the board
MOT_R_N: D504.1 (K), Q504.1 (S), Q504.5 (D), Q504.6 (D), TP506.1, U501.21 (BOUT2); also elsewhere on the board
MOT_R_P: D503.1 (K), Q503.1 (S), Q503.5 (D), Q503.6 (D), TP505.1, U501.28 (BOUT1); also elsewhere on the board
SPI1_MISO: R517.1, TP515.1, U501.17 (SDATO); also elsewhere on the board
SPI1_MOSI: TP514.1, U501.15 (SDATI); also elsewhere on the board
SPI1_SCK_BUS: TP513.1, U501.14 (SCLK); also elsewhere on the board
VBAT: C502.1, C503.1, C505.1, C506.1, C507.1, C508.1, C509.2, Q501.7 (D), Q501.8 (D), Q502.7 (D), Q502.8 (D), Q503.7 (D), Q503.8 (D), Q504.7 (D), Q504.8 (D), U501.4 (VM); also elsewhere on the board

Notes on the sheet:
B1 / B2: CSD88537ND, FET1 high side, FET2 low side; 0 Ohm gate R at each FET (edge-rate trim). SS34 from GND to each phase node: freewheel at -0.36 V, not the -0.73 V body diode (phase pins abs max -0.6 V, S2). R512 50 mOhm: the motor current flows straight through it; Kelvin taps from its inner pa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
Test points: motor current, phases, PWM, SPI
Bridge B: right MG310 (MOT_R_P / MOT_R_N)
VM (pin 4): C507 220 uF bulk (>= 100 uF, 600 mA ripple) + C508 10 nF at the pin. VCP: C509 1 uF to VM. CP1-CP2: C510 100 nF, >= VM + 12 V. V5 100 nF, VINT 1 uF, BEMF 1 nF C0G (SLVSC40 p.3-4).
DRV8711 gate driver (PWMMODE 1, D-002)
nFAULT, nSTALL: open drain, 10k to +3V3. SDATO is open drain on the shared MISO: 2.2k (tau ~66 ns, SPI <= 4 MHz). nSLEEP: 10k pull-down, no internal pull, so the driver sleeps while the MCU is in reset (SLVSC40 p.3). PWMMODE 1: TIM1 drives AIN1/AIN2/BIN1/BIN2 directly (indexer bypassed). Firmware: 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
A1 / A2: CSD88537ND, FET1 high side, FET2 low side; 0 Ohm gate R at each FET (edge-rate trim). SS34 from GND to each phase node: freewheel at -0.36 V, not the -0.73 V body diode (phase pins abs max -0.6 V, S2). R509 50 mOhm: the motor current flows straight through it; Kelvin taps from its inner pa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
Bridge A: left MG310 (MOT_L_P / MOT_L_N)
